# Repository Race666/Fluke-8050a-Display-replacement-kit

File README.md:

# Yet another Fluke 8050a Display replacement kit

There already several cool other projects for a creating a new display for this type of multimeter where the LCD display is broken.

Here are some examples. 
* [vondervotteimittiss.de](https://www.vondervotteimittiss.de/post/a-new-led-display-for-a-fluke-8050a-multimeter)
* [sps-wagner.de](https://www.sps-wagner.de/Sonstiges/8050A.html)
* [hackaday.com](https://hackaday.com/2022/06/17/hacking-a-new-display-into-a-fluke-8050a-multimeter/)

Based on their work I created my own version. My goal was to create a solution that is easy to install.

 So the honer for reverse engineering of the 8050a goes to [Michael Damkier](https://www.vondervotteimittiss.de/) and also to [jasonacox](https://github.com/jasonacox) for the TM1637TinyDisplay library on which my project based.

My project uses an Atmel atmega328p microcontroller which I used for other [projects](https://github.com/Race666/masterclock) too.

The precompiled firmware file could be found [here](./src/pio/.pio/build/ATmega328P/firmware.hex)

Flash the with these fuses (8MHz internal clock)
```
avrdude -c usbtiny -p atmega328p -U lfuse:w:0x62:m -U hfuse:w:0xDE:m -U efuse:w:0x05:m -U flash:w:./src/pio/.pio/build/ATmega328P/firmware.hex
```

Overview over the project folders
| Folder  | Description  |
|---|---|
|[/images](./images)|Images for this wiki|
|[/LogicAnalysis](./LogicAnalysis)|Images with Pulseview Screenshots|
|[/pcb](./pcb)|KiCad project with schematic and PCB|
|[/src](./src)|Platform IO firmware project for atmega328p|
|[/stl](./stl)|3D Data for display- and heatsink holder|

The project has multipe parts

* The platform IO firmware [project](./src/) for the atmega328p microcontroller
* 4 Layer display [PCB](./pcb/) create with KiCad
* A [Display holder](./stl/Fluke%208050a%20Displayhalter.stl) STL for printing by a 3D printer so that the display exctly fits in :-)
* A [holder](./stl/Halter%20Kühlkörper.stl) for a heat sink for the -5V regulator on the mainboard. The Display board consumes more power then the LCD Display so the -5V regulator needs some cooling

In addition to [vondervotteimittiss.de](https://www.vondervotteimittiss.de/post/a-new-led-display-for-a-fluke-8050a-multimeter) I also analysed the logic of the J1 connector from the Fluke display board. I traced the signals by a Hantek logic analyser and pulseview. The traces can be shows [here](./LogicAnalysis/) and looks like this example (Output Pins are the atmega328p outputs for LED's):

It's always the same format. The DIGIT (select) Pins are corrosponding to the Fluke Display from left to right. 

    Fluke Digit Count
                 _    _    _    _
             |  | |  | |  | |  | | 
         +/-     -    -    -    -
             |  | |  | |  | |  | | 
                 ͞     ͞     ͞     ͞        
     Digit  0    1    2    3    4    

When one of the digit pins get's high the data are submitted by the Pins Z, Y, X, W, HV, DP. A schematic/Service Manual of the Fluke 8050a can be found [here](https://xdevs.com/doc/Fluke/FLUKE%208050A%20Instruction.pdf) or [here](http://manuals.chudov.com/Fluke-8050A.pdf). See Page 7-4, 7-5, the DIGITx signal are labeled as STx in the schematic.

When DIGIT 1-4 are set the Pins Z, Y, X, W represents(as 4Bits) the number which is show at the display. While Z is the LSB (Least Significant Bit) and W the MSB (Most Significant Bit) and the DP signals where to position the decimal point in the display. The decimal point must be shown left to the current transmitted digit. For example (see logic trace) if the DP flag is set in digit 3 then the decimal point is between digit 2 and 3.

DIGIT 0 transfer some more information over Z, Y, X, W, HV, DP.
* HV signals the High Voltage info
* DP in digit 0 signals a relative measure/the relative measure button is locked
* When Z is set "1" is shown at digit postition 0
* When X is not set the measure is negative

|   |   |   |   |
|---|---|---|---|
| W=1 | X=1 | Y=0 | Voltage/Current measure          |
| W=1 | X=0 | Y=0 | negative Voltage/Current measure | 
| W=1 | X=0 | Y=1 | Decibel measure                  |
| W=0 | X=0 | Y=0 | Resistor measure                 |

## The LED display board
The LED display board is a 4 layer PCB created by [KiCad](https://www.kicad.org "Great tool"). Where I used very common parts:
* Atmega328p microcontroller
* TM1637 LED 7 segment driver
* 3361BS 7 segment displays

The display board has 4 Leds below the 7 segment displays to signal high voltage, decibel and relative measure.

The 6 Pin header is an atmega ISP port.
| Pin | Signal |
|---|---|
|1| MISO |
|2|VCC|
|3|SCK|
|4|MOSI|
|5|RST|
|6|GND|

The header pins for connecting to the fluke display board are ordered so wiring is simple:

## 3D printer parts

### Holder for the PCB

### Heatsinkholder/stabilizer

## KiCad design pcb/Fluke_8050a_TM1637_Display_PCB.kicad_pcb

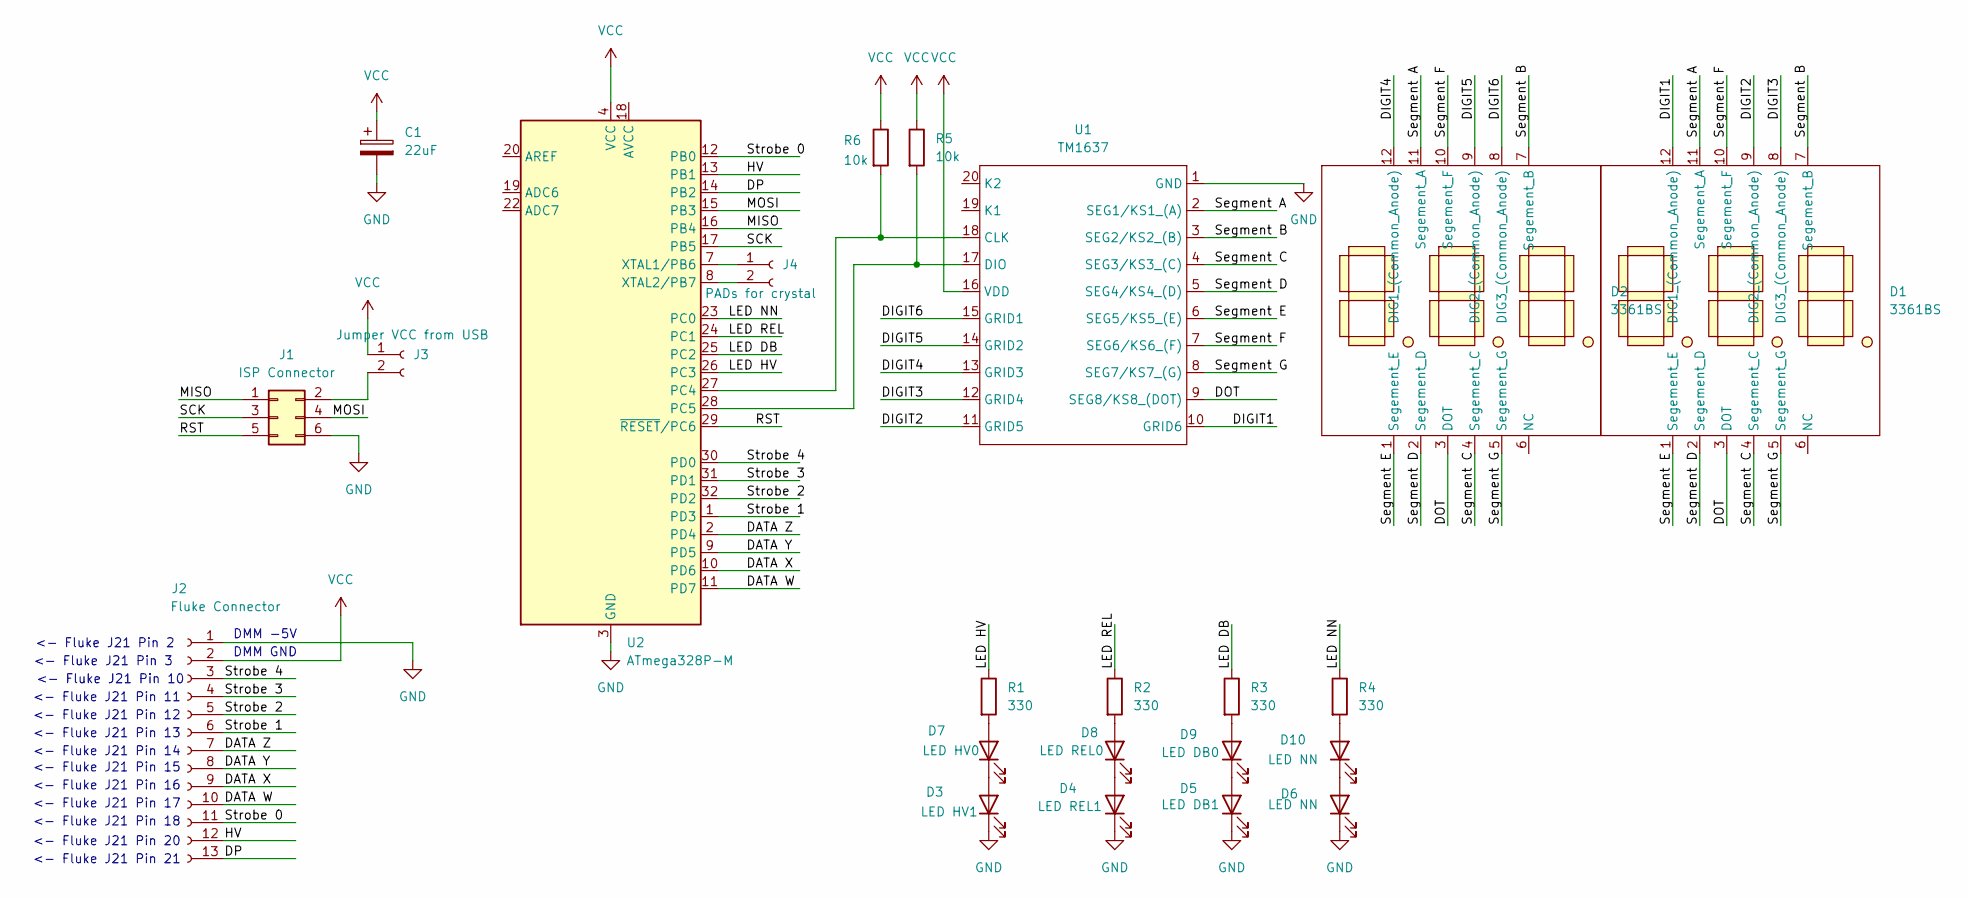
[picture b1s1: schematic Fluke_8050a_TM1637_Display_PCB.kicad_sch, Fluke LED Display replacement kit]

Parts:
C1: 22uF; CP_Elec_4x5.8
D1, D2: 3361BS; 3361xS
D3: LED HV1; LED 5x2mm Exact
D4: LED REL1; LED 5x2mm Exact
D5: LED DB1; LED 5x2mm Exact
D6, D10: LED NN; LED 5x2mm Exact
D7: LED HV0; LED 5x2mm Exact
D8: LED REL0; LED 5x2mm Exact
D9: LED DB0; LED 5x2mm Exact
J1: ISP Connector; PinHeader_2x03_P2.54mm_Vertical
J2: Fluke Connector; PinHeader_1x13_P2.54mm_Vertical
J3: Jumper VCC from USB; PinHeader_1x02_P2.54mm_Vertical
J4: PADs for crystal; PinHeader_1x02_P2.54mm_Vertical
R1, R2, R3, R4: 330; R_0805_2012Metric
R5, R6: 10k; R_0805_2012Metric
U1: TM1637; SOP-20_7.5x12.8mm_P1.27mm
U2: ATmega328P-M; LQFP-32_7x7mm_P0.8mm

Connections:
/DATA W: J2.10, U2.11 (PD7)
/DATA X: J2.9, U2.10 (PD6)
/DATA Y: J2.8, U2.9 (PD5)
/DATA Z: J2.7, U2.2 (PD4)
/DIGIT1: D1.12 (DIG1_(Common_Anode)), U1.10 (GRID6)
/DIGIT2: D1.9 (DIG2_(Common_Anode)), U1.11 (GRID5)
/DIGIT3: D1.8 (DIG3_(Common_Anode)), U1.12 (GRID4)
/DIGIT4: D2.12 (DIG1_(Common_Anode)), U1.13 (GRID3)
/DIGIT5: D2.9 (DIG2_(Common_Anode)), U1.14 (GRID2)
/DIGIT6: D2.8 (DIG3_(Common_Anode)), U1.15 (GRID1)
/DOT: D1.3 (DOT), D2.3 (DOT), U1.9 (SEG8/KS8_(DOT))
/DP: J2.13, U2.14 (PB2)
/HV: J2.12, U2.13 (PB1)
/LED DB: R3.1, U2.25 (PC2)
/LED HV: R1.1, U2.26 (PC3)
/LED NN: R4.1, U2.23 (PC0)
/LED REL: R2.1, U2.24 (PC1)
/MISO: J1.1, U2.16 (PB4)
/MOSI: J1.4, U2.15 (PB3)
/RST: J1.5, U2.29 (~RESET/PC6)
/SCK: J1.3, U2.17 (PB5)
/Segment A: D1.11 (Segement_A), D2.11 (Segement_A), U1.2 (SEG1/KS1_(A))
/Segment B: D1.7 (Segement_B), D2.7 (Segement_B), U1.3 (SEG2/KS2_(B))
/Segment C: D1.4 (Segement_C), D2.4 (Segement_C), U1.4 (SEG3/KS3_(C))
/Segment D: D1.2 (Segement_D), D2.2 (Segement_D), U1.5 (SEG4/KS4_(D))
/Segment E: D1.1 (Segement_E), D2.1 (Segement_E), U1.6 (SEG5/KS5_(E))
/Segment F: D1.10 (Segement_F), D2.10 (Segement_F), U1.7 (SEG6/KS6_(F))
/Segment G: D1.5 (Segement_G), D2.5 (Segement_G), U1.8 (SEG7/KS7_(G))
/Strobe 0: J2.11, U2.12 (PB0)
/Strobe 1: J2.6, U2.1 (PD3)
/Strobe 2: J2.5, U2.32 (PD2)
/Strobe 3: J2.4, U2.31 (PD1)
/Strobe 4: J2.3, U2.30 (PD0)
GND: C1.2, D3.1 (K), D4.1 (K), D5.1 (K), D6.1 (K), J1.6, J2.1, U1.1 (GND), U2.3 (GND), U2.5 (GND), U2.21 (GND), U2.33 (GND)
unnamed: D3.2 (A), D7.1 (K)
unnamed: D4.2 (A), D8.1 (K)
unnamed: D5.2 (A), D9.1 (K)
unnamed: D7.2 (A), R1.2
unnamed: D8.2 (A), R2.2
unnamed: D9.2 (A), R3.2
unnamed: D10.2 (A), R4.2
unnamed: D6.2 (A), D10.1 (K)
unnamed: J1.2, J3.2
unnamed: J4.1, U2.7 (XTAL1/PB6)
unnamed: J4.2, U2.8 (XTAL2/PB7)
unnamed: R6.2, U1.18 (CLK), U2.27 (PC4)
unnamed: R5.2, U1.17 (DIO), U2.28 (PC5)
VCC: C1.1, J2.2, J3.1, R5.1, R6.1, U1.16 (VDD), U2.4 (VCC), U2.6 (VCC)

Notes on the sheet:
<- Fluke J21 Pin 17
<- Fluke J21 Pin 12
<- Fluke J21 Pin 13
<- Fluke J21 Pin 20
<- Fluke J21 Pin 18
<- Fluke J21 Pin 21
<- Fluke J21 Pin 16
<- Fluke J21 Pin 11
DMM -5V
DMM GND
<- Fluke J21 Pin 3
<- Fluke J21 Pin 10
<- Fluke J21 Pin 2
<- Fluke J21 Pin 15
<- Fluke J21 Pin 14

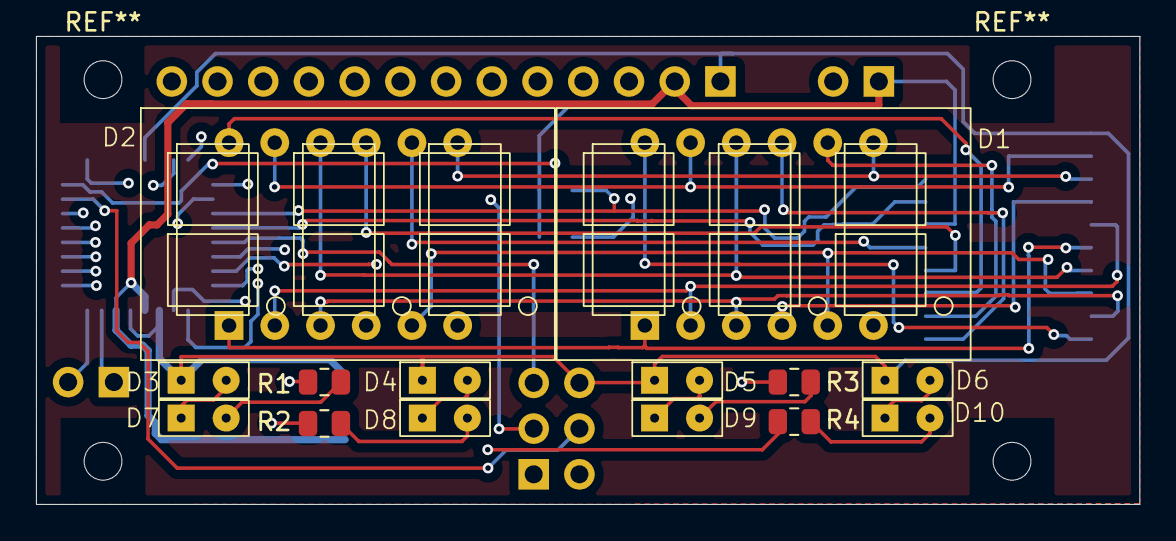
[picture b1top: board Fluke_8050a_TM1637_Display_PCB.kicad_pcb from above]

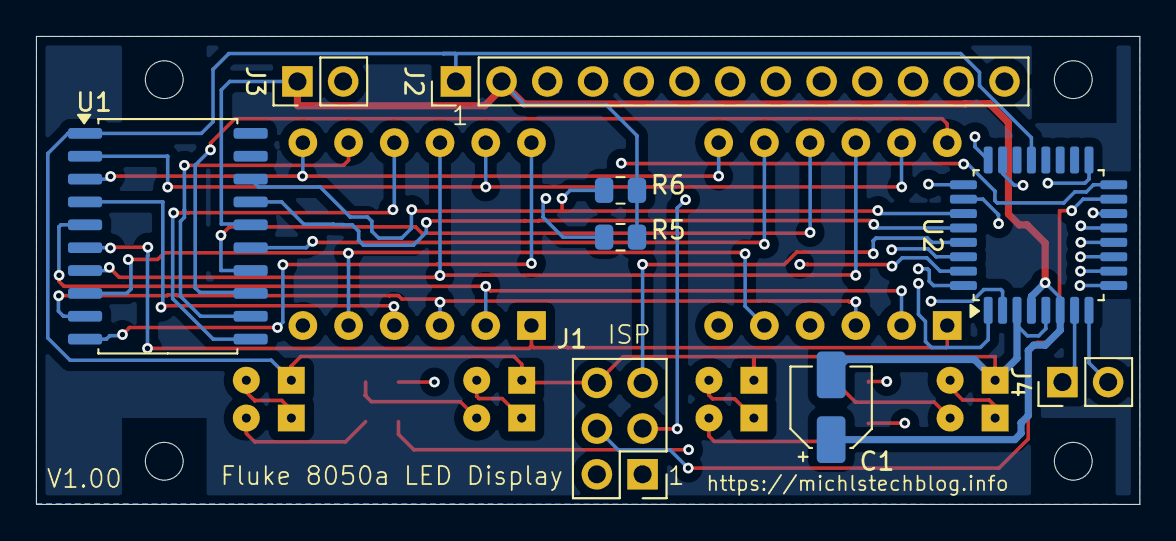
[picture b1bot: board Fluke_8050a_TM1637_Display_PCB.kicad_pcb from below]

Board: 4 copper layers, 61.3 x 26.0 mm, 23 parts (9 on the bottom side), 48 nets.

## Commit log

2025-06-26 Release
2025-06-27 Typo J1 21 fixed
